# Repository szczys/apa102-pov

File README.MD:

APA102-POV
==========

This is a persistence of vision display using the APA102 RGB LED modules. I whipped this design up on the spot at Anool Mahidharia's KiCAD workshop (I hadn't relaly planned ahead to have a design ready). It is untested and definitely a work in progress.

Features:
---------

* 17 RGB Pixels (2 rows of 5x7 characters with a row in between and on either edge)
* IR receiver to issue commands as the display spins
* Hall effect sensor to know precisely where/when each revolution begins

TODO:
-----

* Figure out a method to spin this display
* Find a 5V supply for this board
* Write the code

Future Additions:
-----------------

* I broke out RX/TX pins. It would be fun to add an ESP8266 module to make it WiFi connected
* Power transfer from the base which probably means I need a second regulator circuit

License:
--------

Hardware design is by Mike Szczys and licensed [CC-BY-SA 3.0](https://creativecommons.org/licenses/by-sa/3.0/us/)

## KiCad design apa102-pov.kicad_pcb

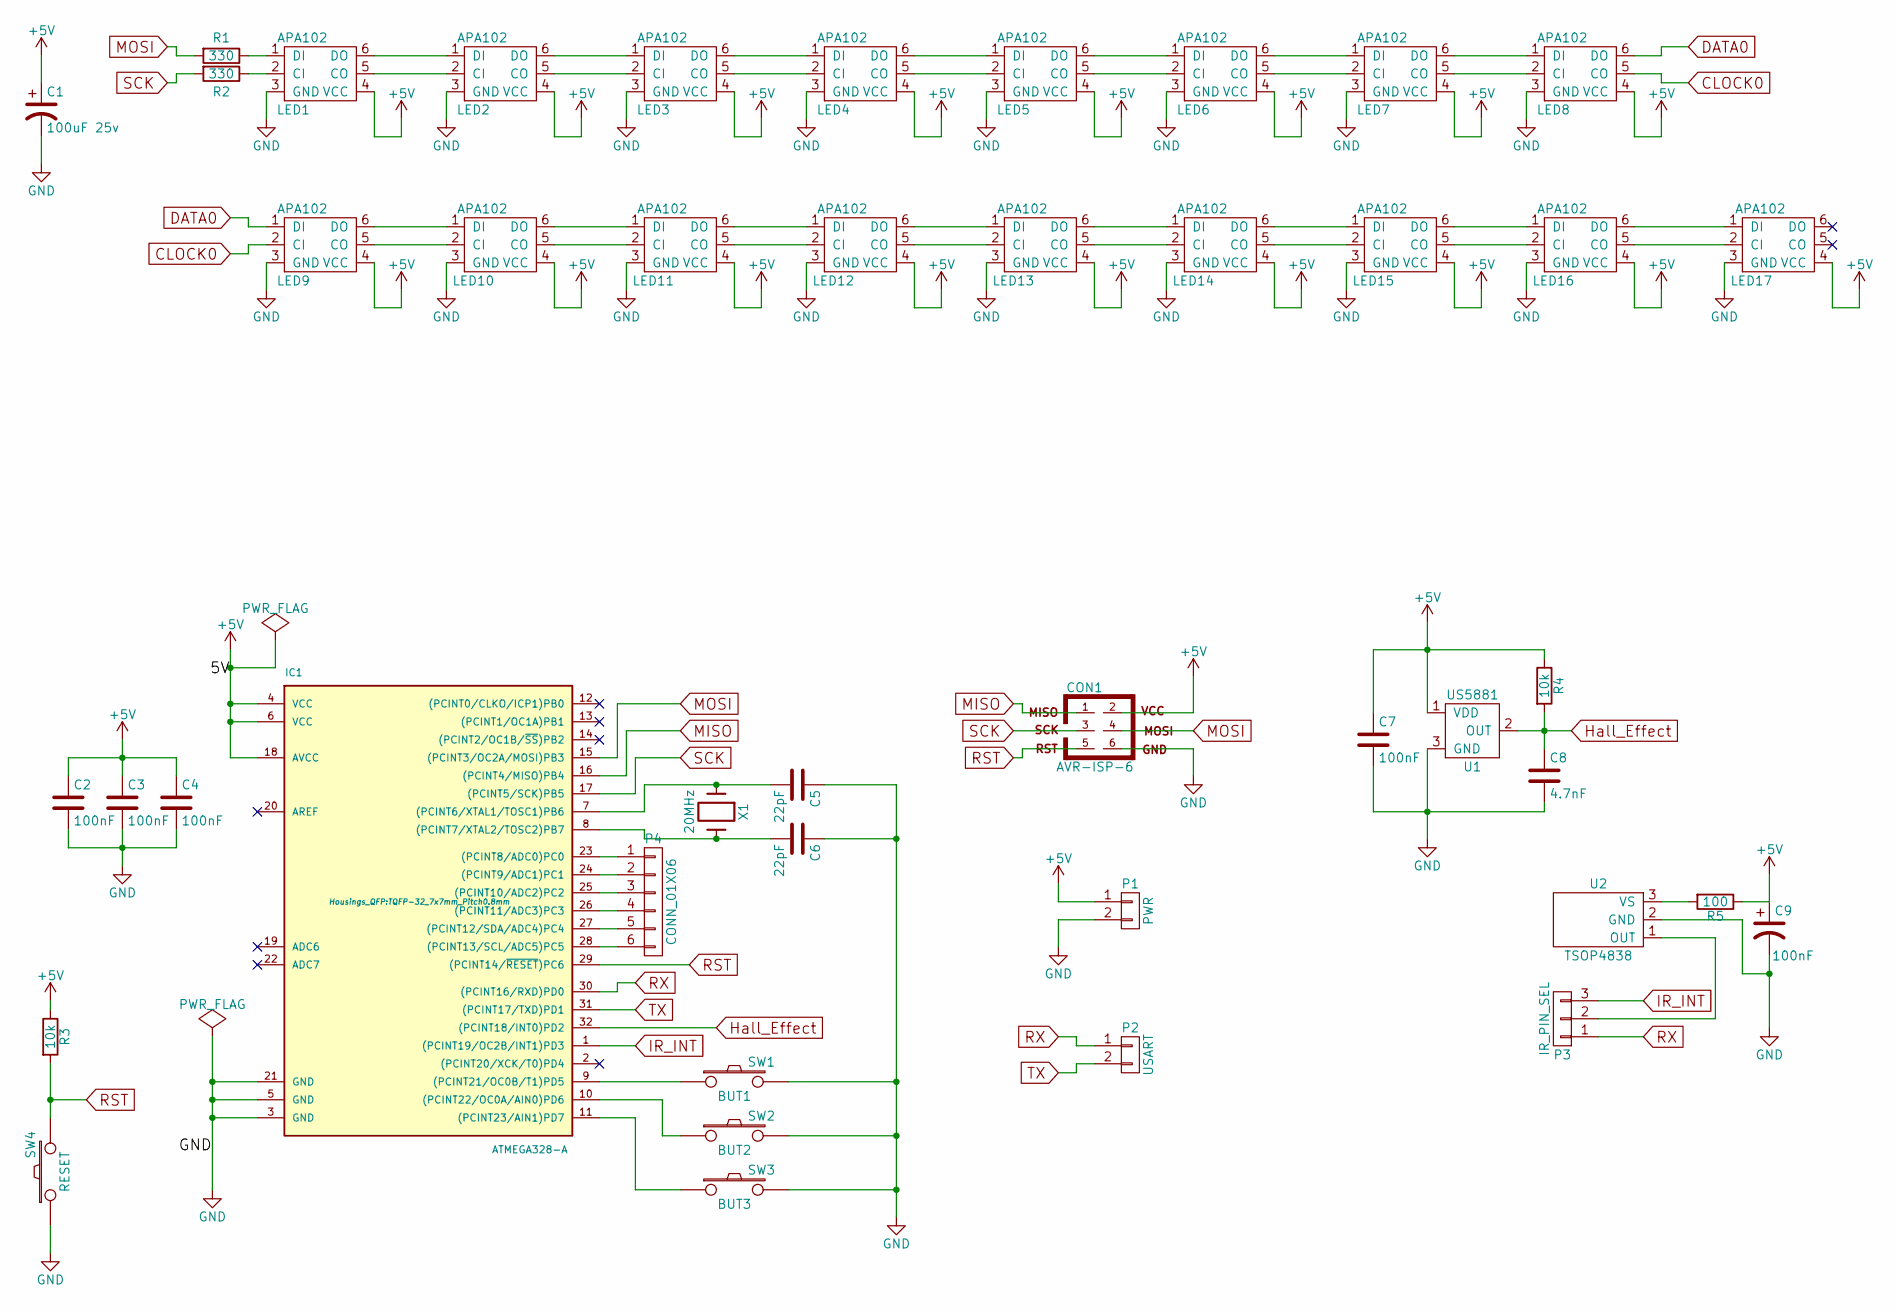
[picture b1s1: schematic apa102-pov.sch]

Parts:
C1: 100uF 25v; c_elec_6.3x5.3
C2, C3, C4, C7, C9: 100nF; C_0805
C5, C6: 22pF; C_0805
C8: 4.7nF; C_0805
CON1: AVR-ISP-6; Pin_Header_Straight_2x03
IC1: ATMEGA328-A; TQFP-32_7x7mm_Pitch0.8mm
LED1, LED2, LED3, LED4, LED5, LED6, LED7, LED8, LED9, LED10, LED11, LED12, LED13, LED14, LED15, LED16, LED17: APA102
P1: PWR; Pin_Header_Straight_1x02
P2: USART; Pin_Header_Straight_1x02
P3: IR_PIN_SEL; Pin_Header_Straight_1x03
P4: CONN_01X06; Pin_Header_Straight_1x06
R1, R2: 330; R_0805
R3, R4: 10k; R_0805
R5: 100; R_0805
SW1: BUT1; SW_PUSH_SMALL
SW2: BUT2; SW_PUSH_SMALL
SW3: BUT3; SW_PUSH_SMALL
SW4: RESET; SW_PUSH_SMALL
U1: US5881; SOT-23
U2: TSOP4838
X1: 20MHz; Q_49U3HMS

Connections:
+5V: C1.1, C2.1, C3.1, C4.1, C7.1, C9.1, CON1.2, IC1.4 (VCC), IC1.6 (VCC), IC1.18 (AVCC), LED1.4 (VCC), LED2.4 (VCC), LED3.4 (VCC), LED4.4 (VCC), LED5.4 (VCC), LED6.4 (VCC), LED7.4 (VCC), LED8.4 (VCC), LED9.4 (VCC), LED10.4 (VCC), LED11.4 (VCC), LED12.4 (VCC), LED13.4 (VCC), LED14.4 (VCC), LED15.4 (VCC), LED16.4 (VCC), LED17.4 (VCC), P1.1, R3.1, R4.1, R5.1, U1.1 (VDD); also elsewhere on the board
CLOCK0: LED8.5 (CO), LED9.2 (CI)
DATA0: LED8.6 (DO), LED9.1 (DI)
GND: C1.2, C2.2, C3.2, C4.2, C5.1, C6.1, C7.2, C8.2, C9.2, CON1.6, IC1.3 (GND), IC1.5 (GND), IC1.21 (GND), LED1.3 (GND), LED2.3 (GND), LED3.3 (GND), LED4.3 (GND), LED5.3 (GND), LED6.3 (GND), LED7.3 (GND), LED8.3 (GND), LED9.3 (GND), LED10.3 (GND), LED11.3 (GND), LED12.3 (GND), LED13.3 (GND), LED14.3 (GND), LED15.3 (GND), LED16.3 (GND), LED17.3 (GND), P1.2, SW1.2, SW2.2, SW3.2, SW4.1, U1.3 (GND), U2.2 (GND); also elsewhere on the board
Hall_Effect: C8.1, IC1.32 ((PCINT18/INT0)PD2), R4.2, U1.2 (OUT)
IR_INT: IC1.1 ((PCINT19/OC2B/INT1)PD3), P3.3
MISO: CON1.1, IC1.16 ((PCINT4/MISO)PB4); also elsewhere on the board
MOSI: CON1.4, IC1.15 ((PCINT3/OC2A/MOSI)PB3), R1.2; also elsewhere on the board
unnamed: C5.2, IC1.7 ((PCINT6/XTAL1/TOSC1)PB6), X1.1
unnamed: C6.2, IC1.8 ((PCINT7/XTAL2/TOSC2)PB7), X1.2
unnamed: IC1.9 ((PCINT21/OC0B/T1)PD5), SW1.1
unnamed: IC1.10 ((PCINT22/OC0A/AIN0)PD6), SW2.1
unnamed: IC1.11 ((PCINT23/AIN1)PD7), SW3.1
unnamed: IC1.23 ((PCINT8/ADC0)PC0), P4.1
unnamed: IC1.24 ((PCINT9/ADC1)PC1), P4.2
unnamed: IC1.25 ((PCINT10/ADC2)PC2), P4.3
unnamed: IC1.26 ((PCINT11/ADC3)PC3), P4.4
unnamed: IC1.27 ((PCINT12/SDA/ADC4)PC4), P4.5
unnamed: IC1.28 ((PCINT13/SCL/ADC5)PC5), P4.6
unnamed: LED1.1 (DI), R1.1
unnamed: LED1.2 (CI), R2.1
unnamed: LED1.5 (CO), LED2.2 (CI)
unnamed: LED1.6 (DO), LED2.1 (DI)
unnamed: LED2.5 (CO), LED3.2 (CI)
unnamed: LED2.6 (DO), LED3.1 (DI)
unnamed: LED3.5 (CO), LED4.2 (CI)
unnamed: LED3.6 (DO), LED4.1 (DI)
unnamed: LED4.5 (CO), LED5.2 (CI)
unnamed: LED4.6 (DO), LED5.1 (DI)
unnamed: LED5.5 (CO), LED6.2 (CI)
unnamed: LED5.6 (DO), LED6.1 (DI)
unnamed: LED6.5 (CO), LED7.2 (CI)
unnamed: LED6.6 (DO), LED7.1 (DI)
unnamed: LED7.5 (CO), LED8.2 (CI)
unnamed: LED7.6 (DO), LED8.1 (DI)
unnamed: LED9.6 (DO), LED10.1 (DI)
unnamed: LED9.5 (CO), LED10.2 (CI)
unnamed: LED10.5 (CO), LED11.2 (CI)
unnamed: LED10.6 (DO), LED11.1 (DI)
unnamed: LED11.5 (CO), LED12.2 (CI)
unnamed: LED11.6 (DO), LED12.1 (DI)
unnamed: LED12.5 (CO), LED13.2 (CI)
unnamed: LED12.6 (DO), LED13.1 (DI)
unnamed: LED13.5 (CO), LED14.2 (CI)
unnamed: LED13.6 (DO), LED14.1 (DI)
unnamed: LED14.5 (CO), LED15.2 (CI)
unnamed: LED14.6 (DO), LED15.1 (DI)
unnamed: LED15.5 (CO), LED16.2 (CI)
unnamed: LED15.6 (DO), LED16.1 (DI)
unnamed: LED16.5 (CO), LED17.2 (CI)
unnamed: LED16.6 (DO), LED17.1 (DI)
unnamed: P3.2, U2.1 (OUT)
unnamed: R5.2, U2.3 (VS)
RST: CON1.5, IC1.29 ((PCINT14/~RESET~)PC6), R3.2, SW4.2; also elsewhere on the board
RX: IC1.30 ((PCINT16/RXD)PD0), P2.1, P3.1
SCK: CON1.3, IC1.17 ((PCINT5/SCK)PB5), R2.2; also elsewhere on the board
TX: IC1.31 ((PCINT17/TXD)PD1), P2.2

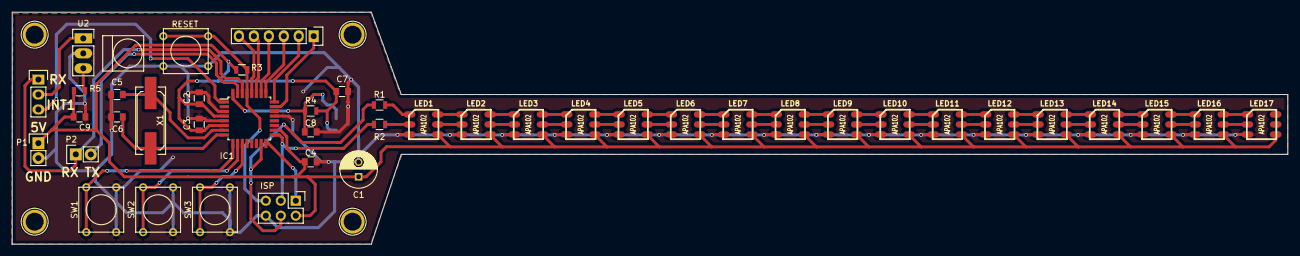
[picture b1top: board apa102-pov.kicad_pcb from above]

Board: 2 copper layers, 216.5 x 39.4 mm, 44 parts (1 on the bottom side), 57 nets.

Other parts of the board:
ISP: AVR-ISP-6; Pin_Header_Straight_2x03
RESET: RESET; SW_PUSH_SMALL

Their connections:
+5V: ISP.2; also elsewhere on the board
GND: ISP.6, RESET.1; also elsewhere on the board
MISO: ISP.1; also elsewhere on the board
MOSI: ISP.4; also elsewhere on the board
RST: ISP.5, RESET.2; also elsewhere on the board
SCK: ISP.3; also elsewhere on the board

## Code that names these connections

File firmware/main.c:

/********************************
* APA102-POV                 	*
* MIT License               	*
* Copyright 2015 - Mike Szczys  *
* http://jumptuck.com 	    	*
*				                *
********************************/

#define F_CPU 20000000

//lfuse: 0b11010111
//  This is 0xD7 for:
//  -No clock divide by 8
//  -Brown-out Detector
//  -Full-swing crystal oscillator (20Mhz)


#include <avr/io.h>
#include <util/delay.h>

#define TOTPIXELS   17
struct Pixels
{
    uint8_t brightness;
    uint8_t r;
    uint8_t g;
    uint8_t b;
} pixel;

struct Pixels pixels[TOTPIXELS];

/************** Setup bitbang LEDs ********************/
#define LED_DDR     DDRB
#define LED_PORT    PORTB     
#define LED_DATA    (1<<PB3)
#define LED_CLOCK   (1<<PB5)

/************** Setup input buttons *********************/
#define BUT_DDR     DDRD
#define BUT_PORT    PORTD
#define BUT_PIN     PIND
#define BUT_SW1     (1<<PD5)
#define BUT_SW2     (1<<PD6)
#define BUT_SW3     (1<<PD7)

/**************** Prototypes *************************************/
void POST(uint8_t pixels, uint8_t brightness);
void startFrame(void);
void endFrame(void);
void pushPixel(uint8_t brightness, uint8_t r, uint8_t g, uint8_t b);
void shiftByte(uint8_t data);
void shiftZero(void);
void shiftOne(void);
void initBuffer(void);
void printBuffer(void);
void init_IO(void);
void init_interrupts(void);
void larsonScanner(uint8_t repeat);
void fadePixelsByHalf(void);
/**************** End Prototypes *********************************/

void POST(uint8_t pixels, uint8_t brightness) {
    //Bit Bang the LEDs to ensure they work despite hardware SPI
    
    uint8_t i = 0;
    startFrame();
    while (i++ <= (pixels/3)) {
        //Shift Red
        pushPixel(brightness, 0xFF, 0x00, 0x00);
        //Shift Green
        pushPixel(brightness, 0x00, 0xFF, 0x00);
        //Shift Blue
        pushPixel(brightness, 0x00, 0x00, 0xFF);
    }
    endFrame();
    
}

void startFrame(void) {
    //Start frame (0*32);
    shiftByte(0x00);    shiftByte(0x00);   shiftByte(0x00);   shiftByte(0x00);
}

void endFrame(void) {
    //End frame (1*32);
    shiftByte(0xFF);    shiftByte(0xFF);   shiftByte(0xFF);   shiftByte(0xFF);
}

void pushPixel(uint8_t brightness, uint8_t r, uint8_t g, uint8_t b) {
    //Brightness only uses 5 LSB. 3 MSB must all be 1
    shiftByte(0b11100000 | brightness);    shiftByte(b);   shiftByte(g);   shiftByte(r);
}
void shiftByte(uint8_t data) {
    for (uint8_t i=0; i<8; i++) {
        if (data & (1<<(7-i))) { shiftOne(); }
        else { shiftZero(); }
    }
}

void shiftZero(void) {
    LED_PORT &= ~LED_DATA;    //low
    LED_PORT |= LED_CLOCK;                  //Raise Clock to shift in Data
    LED_PORT &= ~LED_CLOCK;                  //Clock low
}

void shiftOne(void) {
    LED_PORT |= LED_DATA;                   //Data high
    LED_PORT |= LED_CLOCK;                  //Raise Clock to shift in Data
    LED_PORT &= ~LED_CLOCK;                  //Clock low
}

void initBuffer(void) {
    for (uint8_t i=0; i<TOTPIXELS; i++) {
        pixels[i].brightness = 31;
        pixels[i].r = 0;
        pixels[i].g = 0;
        pixels[i].b = 0;
    }
}

void printBuffer(void) {
    startFrame();
    for (uint8_t i=0; i<TOTPIXELS; i++) {
        pushPixel(pixels[i].brightness, pixels[i].r, pixels[i].g, pixels[i].b);
    }
    endFrame();
}

void init_IO(void) {
    //BitBang LEDS
    LED_DDR |= LED_DATA | LED_CLOCK;
    LED_PORT &= ~(LED_DATA | LED_CLOCK);       //start low
    
    //Buttons
    BUT_DDR &= ~(BUT_SW1 | BUT_SW2 | BUT_SW3);      //Set as input
    BUT_PORT |= BUT_SW1 | BUT_SW2 | BUT_SW3;      //Enable pull-up
}

void init_interrupts(void) {

}

void fadeForever(void) {
    uint8_t fade = 0;
    while(1)
    {
        if (++fade > 31) { fade = 0; }
        startFrame();
        pushPixel(fade, 0xFF, 0x00, 0x00);
        pushPixel(fade, 0x00, 0xFF, 0x00);
        pushPixel(fade, 0x00, 0x00, 0xFF);
        endFrame();
        _delay_ms(20);
    }
}

void rainbowForever(uint8_t pixels, uint8_t brightness, uint8_t repeat) {    
    uint8_t cycleRed = 0xFF;
    uint8_t cycleGreen = 0;
    uint8_t cycleBlue = 0;
    uint8_t cycles = repeat;
    
    if (repeat == 0) { cycles = 1;}

    while(cycles > 0)
    {
        if (repeat == 0) {
            cycles = 1;
        }
        else { --cycles; }
        //down red
        
        while (cycleRed > 0) {
            cycleRed -= 1;
            cycleGreen = 0xFF - cycleRed;
        
            startFrame();
            for (uint8_t i=0; i<pixels; i++) { pushPixel(brightness, cycleRed, cycleGreen, cycleBlue); }
            endFrame();

            _delay_ms(2);
        }
        
        //down green
        while (cycleGreen > 0) {
            cycleGreen -= 1;
            cycleBlue = 0xFF - cycleGreen;
        
            startFrame();
            for (uint8_t i=0; i<pixels; i++) { pushPixel(brightness, cycleRed, cycleGreen, cycleBlue); }
            endFrame();

            _delay_ms(2);
        }

        //down blue
        while (cycleBlue > 0) {
            cycleBlue -= 1;
            cycleRed = 0xFF - cycleBlue;
        
            startFrame();
            for (uint8_t i=0; i<pixels; i++) { pushPixel(brightness, cycleRed, cycleGreen, cycleBlue); }
            endFrame();

            _delay_ms(2);
        }     
    }
}

void larsonScanner(uint8_t repeat) {
    int8_t dir = 1;    //direction
    uint8_t idx = 0;    //index
    uint8_t pixStart = 128; //pixelStartValue
    uint8_t cycles = repeat;
    
    initBuffer();
    pixels[idx].r = pixStart; //light the first pixel
    printBuffer();
    
    if (repeat == 0) {
        // 0 is code for loop forever
        cycles = 1;
    }
    
    while (cycles > 0) {
        
        idx += dir; //Increment the index
        
        //If we're not at one end or the other react accordingly
        if (idx == 0) {
            if (repeat == 0) {
                // 0 is code for loop forever
                cycles = 1;
            }
            else { --cycles; }
            dir = 1;
        }
        if (idx == (TOTPIXELS-1)) { dir = -1; }
        
        //Fade the tail before writing new pixel
        fadePixelsByHalf();
        
        //Write the new pixel
        pixels[idx].r = pixStart;
        
        //Show the changes we've made to the buffer
        printBuffer();
        
        //Delay before next loop
        _delay_ms(20);
    }
}

void fadePixelsByHalf(void) {
    for (uint8_t i=0; i<TOTPIXELS; i++) {
        pixels[i].r = pixels[i].r/2;
        pixels[i].g = pixels[i].g/2;
        pixels[i].b = pixels[i].b/2;
    }
}

int main(void)
{
    init_IO();
    init_interrupts();

    _delay_ms(200);

    POST(TOTPIXELS, 31);
    
    while (BUT_PIN & BUT_SW3) {
        ; //Loop until the button is pressed
    }

    while(1)
    {
        //fadeForever();
        rainbowForever(17, 5, 3);
        
        larsonScanner(4);
    }
}

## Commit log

2015-09-14 Added README.MD
2015-09-14 Added images of schematic, board, and render
2015-09-14 Added image in readme
2015-09-26 Added BOM
2015-09-26 First stab a bit-bang APA102 code
2015-10-12 Fixed SPI clock function when shifting data
2015-10-12 Added functions for all APA102 frame types
2015-10-12 Global fading example
2015-10-12 added rainbow fade example
2015-10-13 Modularized the test functions
2015-10-14 Implemented a frame buffer
2015-10-14 Implemented a Larson Scanner
2015-10-17 Added forever loop to Larson Scanner function Started using 20Mhz external crystal
2015-10-17 rainbow forever can now be constrained

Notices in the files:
apa102-pov.kicad_pcb:
APA102-POV designed by Mike Szczys CC-BY-SA 3.0
